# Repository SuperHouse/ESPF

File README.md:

ESPFlasher ESP8266 / ESP32 Programmer
======================================

Serial programming adapter for the Espressif ESP8266 and ESP32 with
a USB-C connection. Provides a 6-pin connection that includes power,
TX, RX, and the GPIO0 / Reset lines required to put the ESPx into
programming mode.

The pinout is compatible with the "ESPFlash" header convention:

  https://www.superhouse.tv/espflash

Features:

 * USB-C interface for connection to host.
 * ESPFlash 1x6 0.1" header for connection to target board.
 * CP2102N USB-to-serial converter.
 * TX/RX LEDs.
 * 600mA 3.3V voltage regulator to power target board.

You can view more details at:

  https://www.superhouse.tv/espf

Credits
-------
 * Jonathan Oxer <jon@oxer.com.au>

License
-------
Copyright 2019-2020 Superhouse Automation Pty Ltd www.superhouse.tv

The hardware portion of this project is licensed under the TAPR Open
Hardware License (www.tapr.org/OHL). The "license" folder within this
repository also contains a copy of this license in plain text format.

The software portion of this project is licensed under the Simplified
BSD License. The "licence" folder within this project contains a copy
of this license in plain text format.

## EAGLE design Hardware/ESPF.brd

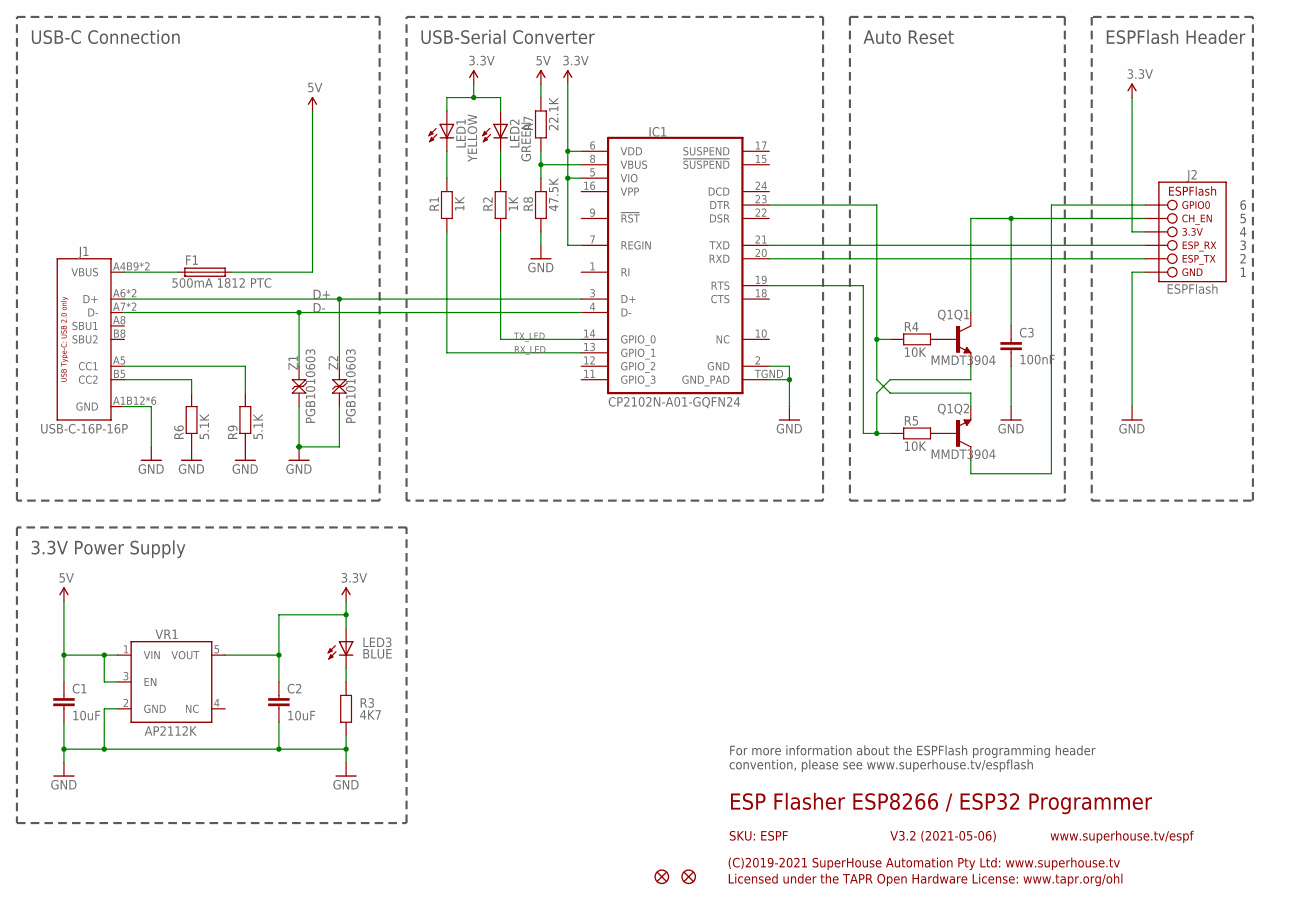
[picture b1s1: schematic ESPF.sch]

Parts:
C1, C2: 10uF; C0603
C3: 100nF; C0603
F1: 500mA 1812 PTC; 1812
FID1, FID2: FIDUCIAL1X2.5; FIDUCIAL-1X2.5
IC1: CP2102N-A01-GQFN24; QFN-24
J1: USB-C-16P-16P; USB-C-16P
J2: ESPFLASH-1X6-2.54-PINS-RA; 1X6-2.54-PINS-RA
LED1: YELLOW; LED-0603
LED2: GREEN; LED-0603
LED3: BLUE; LED-0603
Q1: MMDT3904; SOT-363
R1, R2: 1K; R0603
R3: 4K7; R0603
R4, R5: 10K; R0603
R6, R9: 5.1K; R0603
R7: 22.1K; R0603
R8: 47.5K; R0603
VR1: AP2112K-3.3; SOT23-5
Z1, Z2: PGB1010603; TVS0603

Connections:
3.3V: C2.1, IC1.5 (VIO), IC1.6 (VDD), IC1.7 (REGIN), J2.4 (3.3V), LED1.A, LED2.A, LED3.A, VR1.5 (VOUT)
5V: C1.1, F1.2, R7.2, VR1.1 (VIN), VR1.3 (EN)
D+: IC1.3 (D+), J1.A6 (D+), J1.B6 (D+), Z2.2
D-: IC1.4 (D-), J1.A7 (D-), J1.B7 (D-), Z1.2
DTR: IC1.23 (DTR), Q1.1 (E), R4.1
EN: C3.1, J2.5 (CH_EN), Q1.3 (C)
GND: C1.2, C2.2, C3.2, IC1.2 (GND), IC1.TGND (GND_PAD), J1.A1B12 (GND), J1.A12B1 (GND), J1.FIX1 (GND), J1.FIX2 (GND), J1.FIX3 (GND), J1.FIX4 (GND), J2.1 (GND), R3.1, R6.1, R8.1, R9.1, VR1.2 (GND), Z1.1, Z2.1
GPIO0: J2.6 (GPIO0), Q1.6 (C)
unnamed: LED1.C, R1.2
unnamed: LED2.C, R2.2
unnamed: LED3.C, R3.2
unnamed: IC1.8 (VBUS), R7.1, R8.2
unnamed: Q1.5 (B), R4.2
unnamed: Q1.2 (B), R5.2
unnamed: J1.B5 (CC2), R6.2
unnamed: J1.A5 (CC1), R9.2
RTS: IC1.19 (RTS), Q1.4 (E), R5.1
RXI: IC1.20 (RXD), J2.2 (ESP_TX)
RX_LED: IC1.13 (GPIO_1), R1.1
TXO: IC1.21 (TXD), J2.3 (ESP_RX)
TX_LED: IC1.14 (GPIO_0), R2.1
VIN: F1.1, J1.A4B9 (VBUS), J1.A9B4 (VBUS)

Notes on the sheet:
ESP Flasher ESP8266 / ESP32 Programmer
V3.2 (2021-05-06)
SKU: ESPF
(C)2019-2021 SuperHouse Automation Pty Ltd: www.superhouse.tv
Licensed under the TAPR Open Hardware License: www.tapr.org/ohl
www.superhouse.tv/espf
USB-C Connection
USB-Serial Converter
Auto Reset
ESPFlash Header
3.3V Power Supply
For more information about the ESPFlash programming header convention, please see www.superhouse.tv/espflash

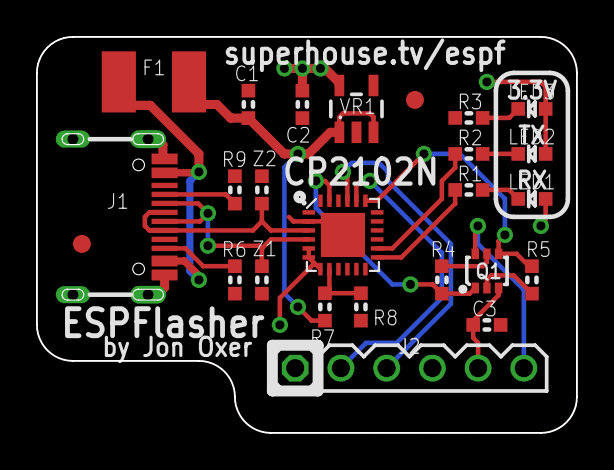
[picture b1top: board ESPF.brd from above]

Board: 2 copper layers, 30.0 x 22.0 mm, 25 parts (0 on the bottom side), 22 nets.

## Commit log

2019-06-21 Initial project import for v1.0 release
2019-06-21 Added render
2019-06-21 Markdown fix
2019-06-21 Renumbered parts
2019-07-01 Replaced most parts using SuperHouse library to add 3D models
2019-07-04 Improved designators
2019-07-04 Replaced CP2104 with CP2102N for v1.1 release
2019-07-07 Split CC1 and CC2 on USB connector
2020-05-25 Major revision of header pinout
2020-05-25 Updated README and render for raname and v3.0
2020-05-27 Fixed dimensions of 6-way right angle header
2020-05-27 Updated render to match new header dimensions
2020-08-13 Begin restructuring project
2020-08-13 Updated README and added licese files
2020-08-14 Added description of test procedure
2020-08-14 Added label for packaging tag
2020-09-08 Fixed spelling mistakes in README. Thanks to Vincent for pointing this out :-)
2020-09-17 Added v3.0 product photos
2020-09-17 Added .gitignore
2021-03-10 Replace ESPFlash header using part from dedicated library.
2021-03-10 Added images.
2021-03-10 Added link to ESPFlash definition.
2021-07-06 Added 100nF cap on reset line of target device. Added tab to support right angle header. Added note about ESPFlash convention in schematic.
2021-07-06 Added Mac icons to .gitignore.
2021-07-06 Added schematic of PDF for release v3.2.
2021-07-06 Updated renders for v3.2 release.

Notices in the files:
ESPF.sch:
(C)2019-2020 SuperHouse Automation Pty Ltd: www.superhouse.tv
